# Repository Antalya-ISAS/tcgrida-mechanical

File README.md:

# Antalya ISAS

## tcGrida's remote-control, vehicle codes, and circuit designs. 

### What is tcGrida?
tcGrida is an explorer ROV that is capable of long duration and long-distance dives, autonomous emergency easy-surface*, live video feed, 4K@60 video recording, high-pressure durable and waterproof design with a wired, trustable and stable connection.

*: A solution that prevents your vehicle from getting lost in the water when the connection is lost and makes it get back to the surface autonomously.

## Our Social Media Accounts, Website and Discord Server

 Instagram: https://instagram.com/antalya.isas
 
 LinkedIn: https://linkedin.com/company/antalya-isas

 YouTube: https://www.youtube.com/channel/UCWZvgA6EhvlmvoRbStbpwaQ

 Website: https://antalyaisas.com

 Discord Server: https://discord.gg/peCKe2drMV

## Contact

E-mail: info@antalyaisas.com

Contact Form: https://antalyaisas.com/iletisim.html

Address: [Molla Yusuf Mah. Hürriyet Cad. No: 25 Konyaaltı/Antalya, Türkiye](https://goo.gl/maps/5YjF16fynHth8VVB9)

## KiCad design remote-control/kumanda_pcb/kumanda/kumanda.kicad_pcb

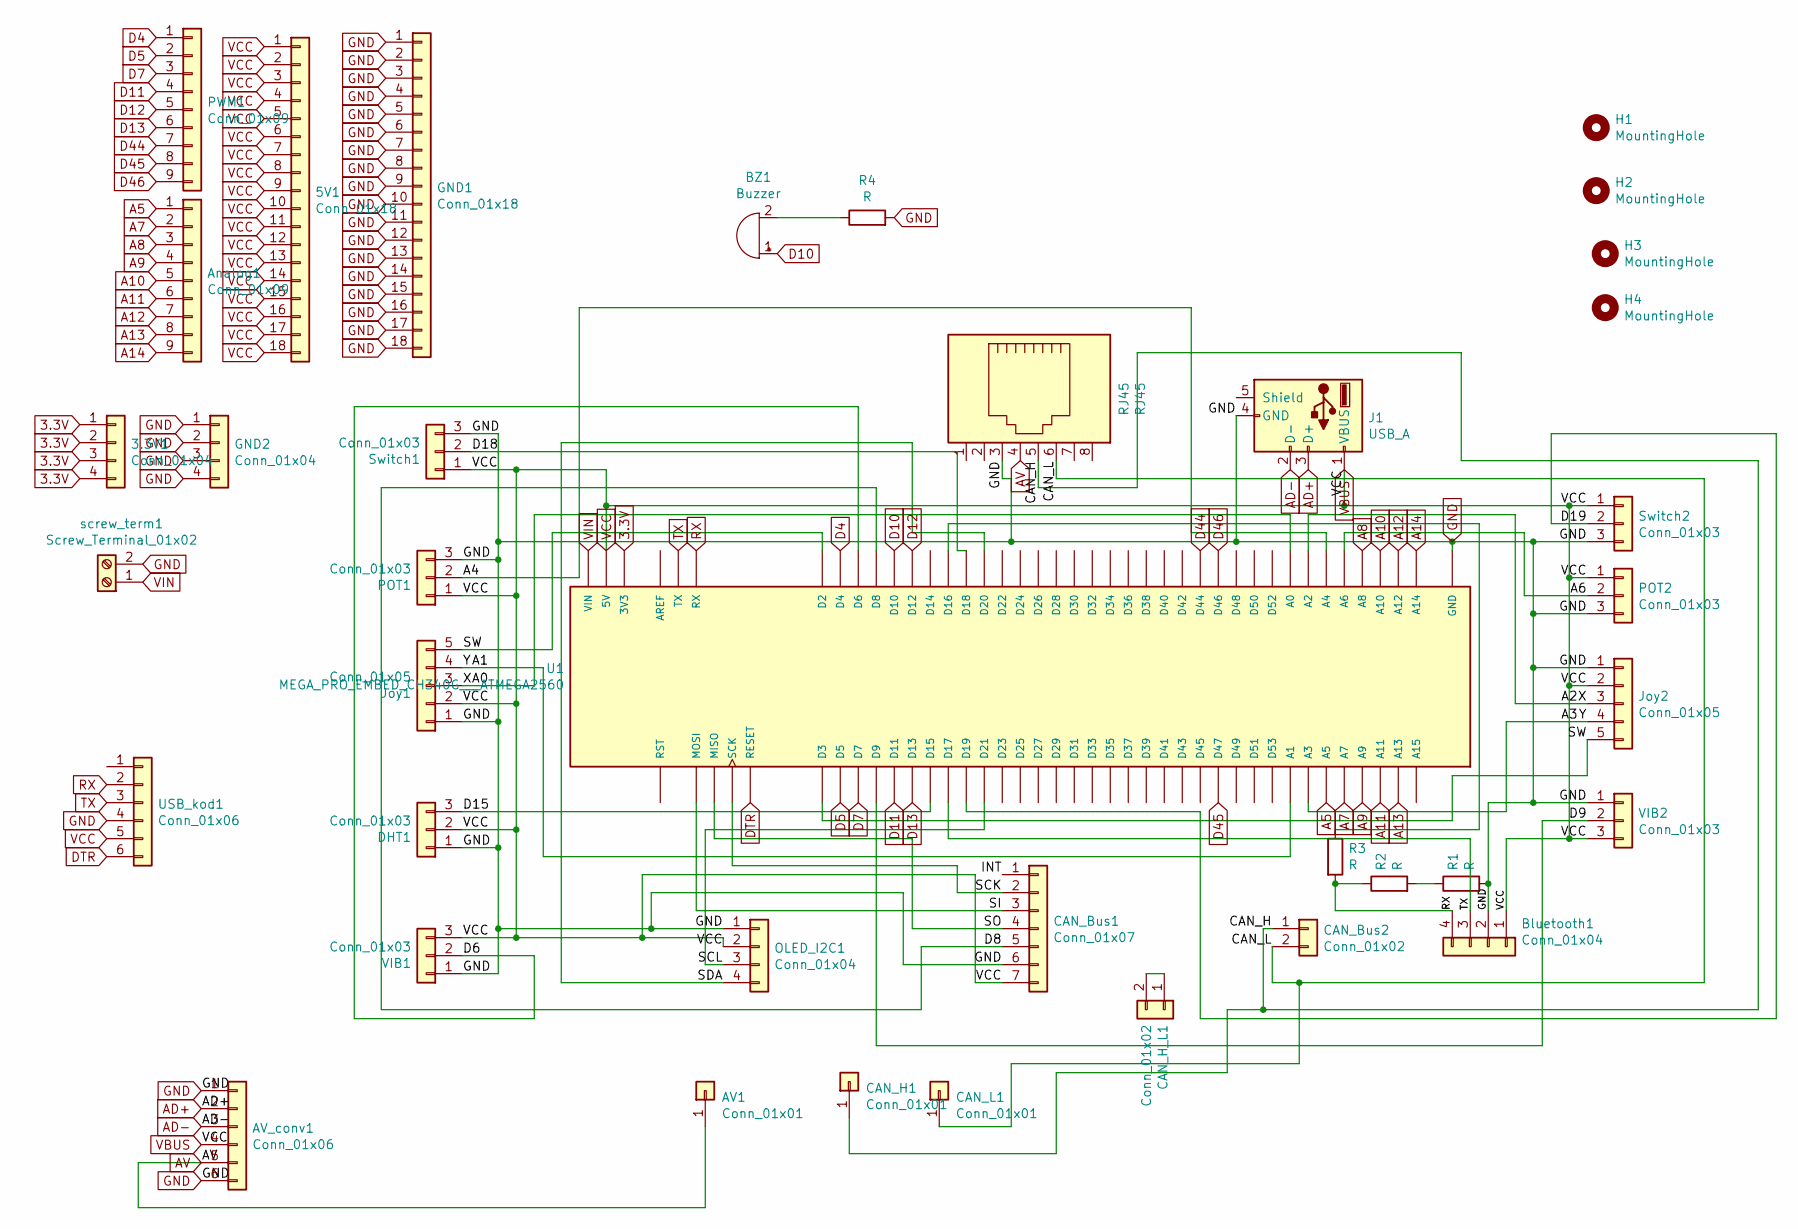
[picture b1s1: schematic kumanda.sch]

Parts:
3.3V1: Conn_01x04; PinHeader_1x04_P2.54mm_Vertical
5V1: Conn_01x18; PinHeader_1x18_P2.54mm_Vertical
AV1: Conn_01x01; PinHeader_1x01_P2.54mm_Vertical
AV_conv1: Conn_01x06; Analog-cam
Analog1: Conn_01x09; PinHeader_1x09_P2.54mm_Vertical
BZ1: Buzzer; Buzzer_12x9.5RM7.6
Bluetooth1: Conn_01x04; JST_XH_B4B-XH-A_1x04_P2.50mm_Vertical
CAN_Bus1: Conn_01x07; PinHeader_1x07_P2.54mm_Vertical
CAN_Bus2: Conn_01x02; PinHeader_1x02_P2.54mm_Vertical
CAN_H1: Conn_01x01; PinHeader_1x01_P2.54mm_Vertical
CAN_H_L1: Conn_01x02; PinHeader_1x02_P2.54mm_Vertical
CAN_L1: Conn_01x01; PinHeader_1x01_P2.54mm_Vertical
DHT1: Conn_01x03; JST_XH_B3B-XH-A_1x03_P2.50mm_Vertical
GND1: Conn_01x18; PinHeader_1x18_P2.54mm_Vertical
GND2: Conn_01x04; PinHeader_1x04_P2.54mm_Vertical
H1, H2, H3, H4: MountingHole; MountingHole_3.2mm_M3
J1: USB_A; USB_A_CONNFLY_DS1095-WNR0
Joy1, Joy2: Conn_01x05; JST_XH_B5B-XH-A_1x05_P2.50mm_Vertical
OLED_I2C1: Conn_01x04; JST_XH_B4B-XH-A_1x04_P2.50mm_Vertical
POT1, POT2: Conn_01x03; JST_XH_B3B-XH-A_1x03_P2.50mm_Vertical
PWM1: Conn_01x09; PinHeader_1x09_P2.54mm_Vertical
R1, R2, R3, R4: R; R_Axial_DIN0207_L6.3mm_D2.5mm_P7.62mm_Horizontal
RJ45: RJ45; RJ45_Ninigi_GE
Switch1, Switch2: Conn_01x03; JST_XH_B3B-XH-A_1x03_P2.50mm_Vertical
U1: MEGA_PRO_EMBED_CH340G___ATMEGA2560; _ATMEGA2560; PARTREV 12/May/2017
USB_kod1: Conn_01x06; PinHeader_1x06_P2.54mm_Vertical
VIB1, VIB2: Conn_01x03; JST_XH_B3B-XH-A_1x03_P2.50mm_Vertical
screw_term1: Screw_Terminal_01x02; TerminalBlock_Phoenix_PT-1,5-2-3.5-H_1x02_P3.50mm_Horizontal

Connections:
3.3V: 3.3V1.1, 3.3V1.2, 3.3V1.3, 3.3V1.4, U1.3V3_1 (3V3), U1.3V3_2 (3V3)
/A0: Joy1.3, Joy2.3, U1.A0, U1.A2
/A1: Joy1.4, Joy2.4, U1.A1, U1.A3
/A4: POT1.2, U1.A4
/A6: POT2.2, U1.A6
/CAN_H: CAN_Bus2.1, CAN_H1.1, RJ45.5
/CAN_L: CAN_Bus2.2, CAN_L1.1, RJ45.6
/D6: U1.D6, VIB1.2
/D8: CAN_Bus1.5, U1.D8
/D9: U1.D9, VIB2.2
/D15: DHT1.3, U1.D15
/D18: Switch1.2, U1.D18
/D19: Switch2.2, U1.D19
/INT: CAN_Bus1.1
/SCK: CAN_Bus1.2, U1.SCK
/SCL: OLED_I2C1.3, U1.D21
/SDA: OLED_I2C1.4, U1.D20
/SI: CAN_Bus1.3, U1.MOSI
/SO: CAN_Bus1.4, U1.MISO
/SW: Joy1.5, Joy2.5, U1.D2, U1.D3
A5: Analog1.1, U1.A5
A7: Analog1.2, U1.A7
A8: Analog1.3, U1.A8
A9: Analog1.4, U1.A9
A10: Analog1.5, U1.A10
A11: Analog1.6, U1.A11
A12: Analog1.7, U1.A12
A13: Analog1.8, U1.A13
A14: Analog1.9, U1.A14
AD+: AV_conv1.2, J1.3 (D+)
AD-: AV_conv1.3, J1.2 (D-)
AV: AV1.1, AV_conv1.5, RJ45.4
D4: PWM1.1, U1.D4
D5: PWM1.2, U1.D5
D7: PWM1.3, U1.D7
D10: BZ1.1 (-), U1.D10
D11: PWM1.4, U1.D11
D12: PWM1.5, U1.D12
D13: PWM1.6, U1.D13
D44: PWM1.7, U1.D44
D45: PWM1.8, U1.D47
D46: PWM1.9, U1.D46
DTR: U1.RESET, USB_kod1.6
GND: AV_conv1.1, AV_conv1.6, Bluetooth1.2, CAN_Bus1.6, DHT1.1, GND1.1, GND1.2, GND1.3, GND1.4, GND1.5, GND1.6, GND1.7, GND1.8, GND1.9, GND1.10, GND1.11, GND1.12, GND1.13, GND1.14, GND1.15, GND1.16, GND1.17, GND1.18, GND2.1, GND2.2, GND2.3, GND2.4, J1.4 (GND), Joy1.1, Joy2.1, OLED_I2C1.1, POT1.3, POT2.3, R1.2, R4.2, RJ45.3, Switch1.3, Switch2.3, U1.GND_1 (GND), U1.GND_2 (GND), U1.GND_3 (GND), USB_kod1.4, VIB1.1, VIB2.1, screw_term1.2
unnamed: BZ1.2 (+), R4.1
unnamed: CAN_H_L1.1, CAN_H_L1.2
unnamed: R1.1, R2.2
unnamed: R3.1, U1.D16
RX: Bluetooth1.4, R2.1, R3.2, U1.RX, USB_kod1.2
TX: Bluetooth1.3, U1.D17, U1.TX, USB_kod1.3
VBUS: 5V1.1, 5V1.2, 5V1.3, 5V1.4, 5V1.5, 5V1.6, 5V1.7, 5V1.8, 5V1.9, 5V1.10, 5V1.11, 5V1.12, 5V1.13, 5V1.14, 5V1.15, 5V1.16, 5V1.17, 5V1.18, AV_conv1.4, Bluetooth1.1, CAN_Bus1.7, DHT1.2, J1.1 (VBUS), Joy1.2, Joy2.2, OLED_I2C1.2, POT1.1, POT2.1, Switch1.1, Switch2.1, U1.5V_1 (5V), U1.5V_2 (5V), U1.5V_3 (5V), USB_kod1.5, VIB1.3, VIB2.3
VIN: U1.VIN_1 (VIN), U1.VIN_2 (VIN), screw_term1.1

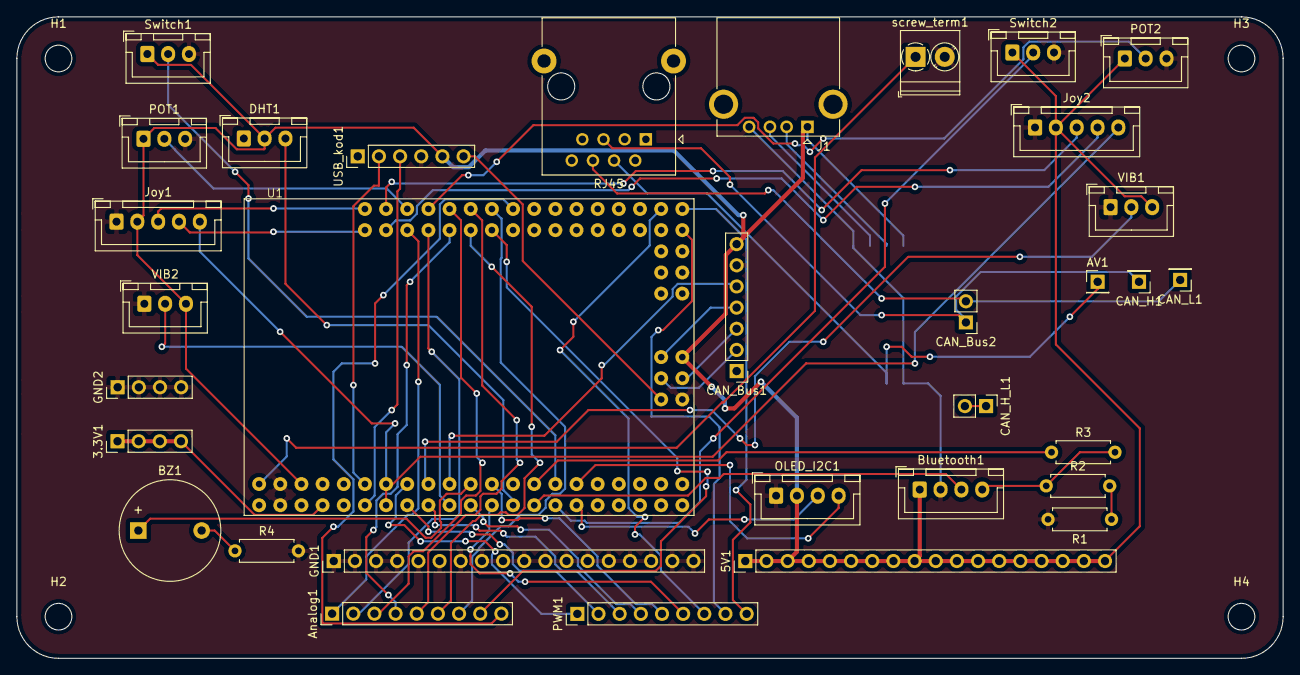
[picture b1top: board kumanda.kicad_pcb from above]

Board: 2 copper layers, 152.0 x 77.0 mm, 38 parts (1 on the bottom side), 51 nets.

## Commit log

2021-07-19 Move mechanical stuff to here from https://github.com/antalya-isas/tcgrida-app
2021-08-13 PCB design finished.

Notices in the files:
README.md:
GPLv3 license
